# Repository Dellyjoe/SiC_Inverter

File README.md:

# SiC-Based Modular Inverter System

## Table of Contents
1. [Project Overview](#1-project-overview)  
2. [System Architecture](#2-system-architecture)  
   - [EMI Input Filter](#21-emi-input-filter)  
   - [Pre‑Charge & Inrush Limiting](#22-pre-charge--inrush-limiting)  
   - [DC‑Link Capacitor Network](#23-dc-link-capacitor-network)  
   - [Inverter Power Stage](#24-inverter-power-stage)  
   - [Output LCL Filter](#25-output-lcl-filter)  
3. [Electrical Specifications](#3-electrical-specifications)  
4. [Development Tools & Equipment](#4-development-tools--equipment)  
5. [Current Status](#5-current-status)  
6. [System Block Diagram](#6-system-block-diagram)

---

## 1. Project Overview

This project is a **modular, SiC‑based single‑phase inverter system** designed using professional engineering practices and a clean, hierarchical architecture. Each functional block is implemented as its own PCB, enabling:

- **Modularity** — swap, upgrade, or debug subsystems independently  
- **Scalability** — expand to higher power levels or new control architectures  
- **Serviceability** — isolate issues quickly during bring‑up  
- **Educational clarity** — each PCB teaches a specific power‑electronics concept  

Key design principles:

- **Hierarchical schematics** (KiCad 9)  
- **Modular PCBs** (EMI filter, pre‑charge, DC‑link, inverter legs, LCL filter, power supplies, controller)  
- **High‑performance SiC MOSFETs** for fast switching and low losses  
- **Low‑inductance DC‑link layout**  
- **Safe, lab‑friendly bring‑up** (initially 60 VDC)  

The long‑term goal is a **flexible, open inverter platform** suitable for experimentation, research, and future expansion.

---

## 2. System Architecture

The inverter is divided into well‑defined functional blocks.

### 2.1 EMI Input Filter
- Differential‑mode LC filter  
  - **L_DM:** `2300HT-470-H-RC`  
  - **C_IN:** `R71PI410050H6K`  
- Common‑mode choke: `7448258022`  
- Provides clean, low‑noise DC to downstream stages  
- **Outputs:** `BUS+_Filtered`, `BUS-_Filtered`

---

### 2.2 Pre‑Charge & Inrush Limiting
- Limits inrush current to **~5 A**  
- Uses an **80 Ω** pre‑charge resistor  
- MOSFET/relay bypass for full‑power operation  
- Interfaces between EMI filter and DC‑link  
- **Outputs:** `DC+`, `DC−`

---

### 2.3 DC‑Link Capacitor Network
- **Bulk Storage:** 220 µF electrolytic (10 × `ESH226M500AL4AA`)  
- **High‑Frequency Film:** 10 µF polypropylene (5 × `MKP1848C52050JK2`)  
- Provides:
  - Energy storage  
  - Low‑impedance switching current path  
  - Reduced ripple and overshoot  

---

### 2.4 Inverter Power Stage
- **Topology:** Full‑bridge using SiC MOSFET half‑bridge legs  
- **Switching Devices:** 4 × Wolfspeed `C3M0025065K`  
- **Gate Drivers:** 4 × TI `UCC21710QDWRQ1` isolated drivers  
- **Sensing:** Placeholders for output current and DC bus voltage (future work)  
- **Control:** PWM interface for microcontroller or DSP  

---

### 2.5 Output LCL Filter
- Shapes PWM into low‑distortion 60 Hz AC  
- Reduces switching ripple and protects the load  
- **Components:**
  - **Series Inductors:**  
    - `L1`: 470 µH (`Bourns 1140-471K-RC`)  
    - `L2`: 470 µH (`Bourns 1140-471K-RC`)  
  - **Shunt Capacitor:**  
    - `C_F`: 6.8 µF, 305 Vac MKP (`KEMET C4AF9BW4680T3FK`)  
  - **Damping Resistor:**  
    - `R_D`: ~10 Ω, ≥3 W (`TE 3-2176794-3`)  
- **Design Target:**  
  - Resonant frequency ≈ 2 kHz  
  - Damped to avoid resonance peaking  

---

## 3. Electrical Specifications

| Parameter | Value | Notes |
|----------|-------|-------|
| **Input Voltage Range** | 335–425 VDC | |
| **Nominal DC Bus Voltage** | 400 VDC | |
| **Output Voltage** | 120 Vrms | Single‑phase AC |
| **Output Frequency** | 60 Hz | |
| **Continuous Power** | 500 W | |
| **Peak Power** | 1 kW | |
| **Continuous Current (RMS)** | 4.1 Arms | Output |
| **Continuous Current (DC)** | 1.25 A | Input at nominal voltage |
| **Switching Frequency** | 40 kHz | Initial target |
| **Target Inrush Current** | < 5 A | Pre‑charge limited |
| **DC‑Link Capacitance** | 220 µF electrolytic + 10 µF film | |
| **Capacitor Voltage Rating** | >500 V | |
| **Output Filter Topology** | LCL | 470 µH – 6.8 µF – 470 µH |

---

## 4. Development Tools & Equipment
- **CAD:** KiCad 9 (hierarchical design)  
- **Version Control:** Git  
- **Documentation:** draw.io, Markdown  
- **Bench Tools:** Oscilloscope, isolated supplies, differential probes  
- *(More tools will be added as the project grows)*  

---

## 5. Current Status

- [x] EMI filter — **Complete**  
- [x] Pre‑charge topology — **Defined**  
- [x] DC‑link architecture — **Defined**  
- [x] KiCad hierarchy — **Modular & clean**  
- [x] Pre‑charge components added  
- [x] DC‑link capacitor bank added  
- [x] Inverter leg schematic started  
- [x] Output LCL filter populated with real parts  
- [x] Inverter + LCL interaction reviewed in simulation  
- [x] Power‑stage support rails (+15V ISO, +3V3 logic)  
- [x] Controller selected  
- [ ] Controller wiring  
- [ ] Layout of sub‑PCBs  
- [ ] System wiring and integration  

---

## 6. System Block Diagram

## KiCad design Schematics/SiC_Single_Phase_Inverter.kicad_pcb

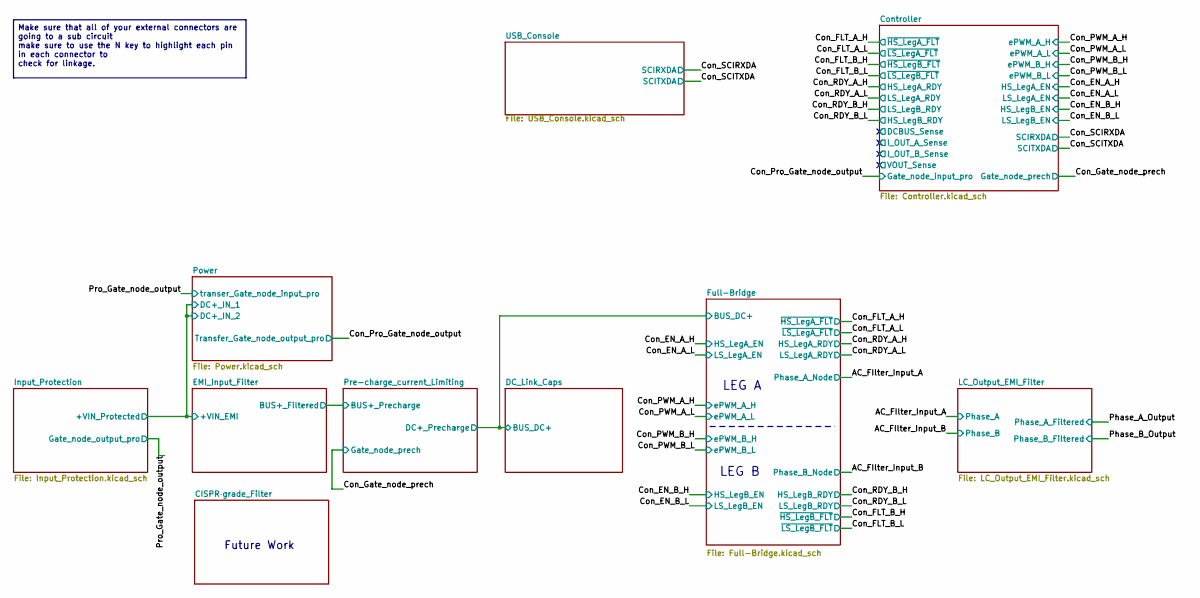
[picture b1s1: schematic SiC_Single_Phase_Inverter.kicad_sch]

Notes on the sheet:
LEG B
Future Work
LEG A
Make sure that all of your external connectors are going to a sub circuit make sure to use the N key to highlight each pin in each connector to check for linkage.

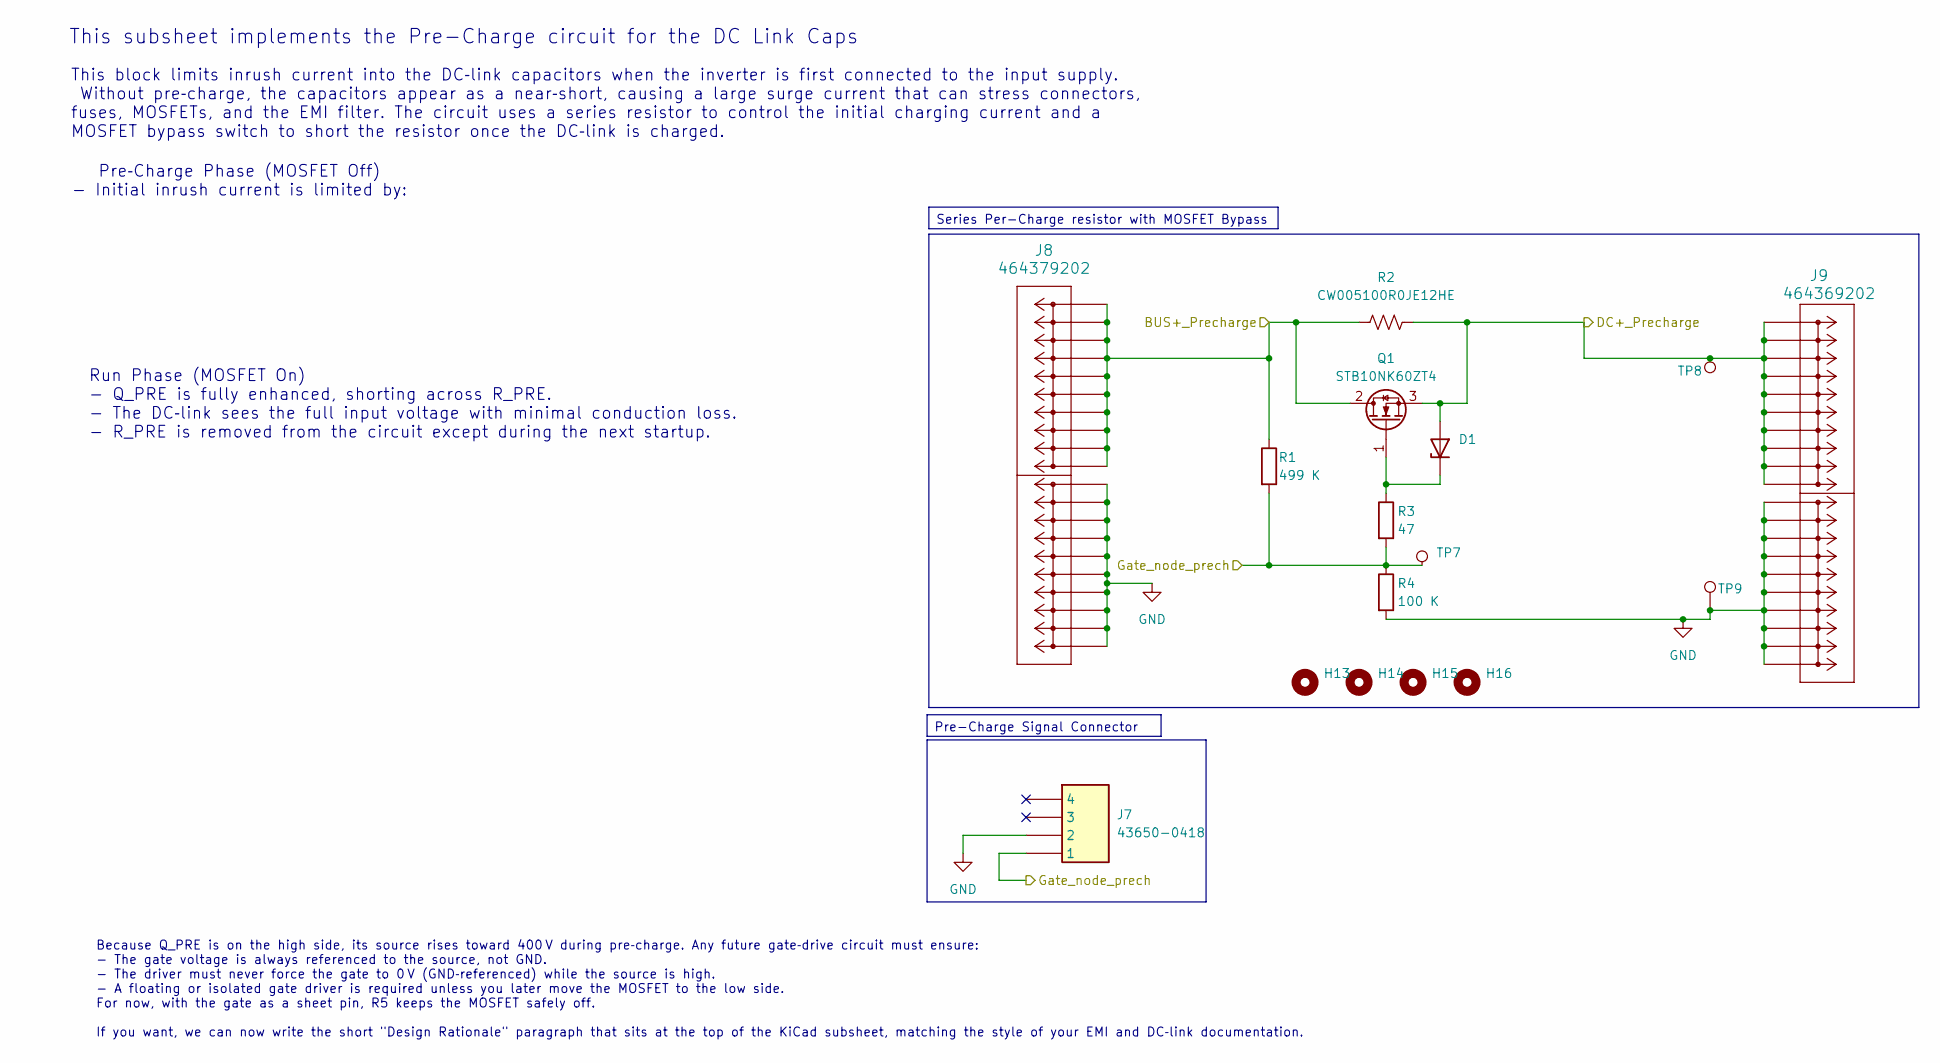
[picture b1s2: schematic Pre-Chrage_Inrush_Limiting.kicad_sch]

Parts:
D1: BZX84C15-7-F; SOT-23-3
H13, H14, H15, H16: MountingHole; MountingHole_2.2mm_M2
J7: 43650-0418; 436500418; Mouser Part Number 538-43650-0418
J8: 464379202; 46437-900_02
J9: 464369202; 46436-900_02
Q1: STB10NK60ZT4; TO-263-2
R1: 499 K; R_1206_3216Metric_Pad1.30x1.75mm_HandSolder
R2: CW005100R0JE12HE
R3: 47; R_1206_3216Metric_Pad1.30x1.75mm_HandSolder
R4: 100 K; R_1206_3216Metric_Pad1.30x1.75mm_HandSolder
TP7, TP8: 5277
TP9: 5281

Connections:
/Con_Gate_node_prech: J7.1, R1.2, R3.2, R4.1, TP7.1 (1_1); also elsewhere on the board
/DC_Link_Caps/BUS_DC+: D1.2 (A), J9.P1_1, J9.P1_2, J9.P1_3, J9.P1_4, J9.P1_5, J9.P1_6, J9.P1_7, J9.P1_8, J9.P1_9, J9.P1_10, Q1.3, R2.2, TP8.1 (1_1); also elsewhere on the board
/EMI_Input_Filter/BUS+_Filtered: J8.P2_1, J8.P2_2, J8.P2_3, J8.P2_4, J8.P2_5, J8.P2_6, J8.P2_7, J8.P2_8, J8.P2_9, J8.P2_10, Q1.2, R1.1, R2.1; also elsewhere on the board
GND: J7.2, J8.P1_1, J8.P1_2, J8.P1_3, J8.P1_4, J8.P1_5, J8.P1_6, J8.P1_7, J8.P1_8, J8.P1_9, J8.P1_10, J9.P2_1, J9.P2_2, J9.P2_3, J9.P2_4, J9.P2_5, J9.P2_6, J9.P2_7, J9.P2_8, J9.P2_9, J9.P2_10, R4.2, TP9.1 (1_1); also elsewhere on the board
unnamed: D1.1 (K), Q1.1 (G), R3.1

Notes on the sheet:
This block limits inrush current into the DC‑link capacitors when the inverter is first connected to the input supply. Without pre‑charge, the capacitors appear as a near‑short, causing a large surge current that can stress connectors, fuses, MOSFETs, and the EMI filter. The circuit uses a series r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
Pre‑Charge Phase (MOSFET Off) - Initial inrush current is limited by:
This subsheet implements the Pre-Charge circuit for the DC Link Caps
Run Phase (MOSFET On) - Q_PRE is fully enhanced, shorting across R_PRE. - The DC‑link sees the full input voltage with minimal conduction loss. - R_PRE is removed from the circuit except during the next startup.
Because Q_PRE is on the high side, its source rises toward 400 V during pre‑charge. Any future gate‑drive circuit must ensure: - The gate voltage is always referenced to the source, not GND. - The driver must never force the gate to 0 V (GND‑referenced) while the source is high. - A floating or iso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
Series Per-Charge resistor with MOSFET Bypass
Pre-Charge Signal Connector

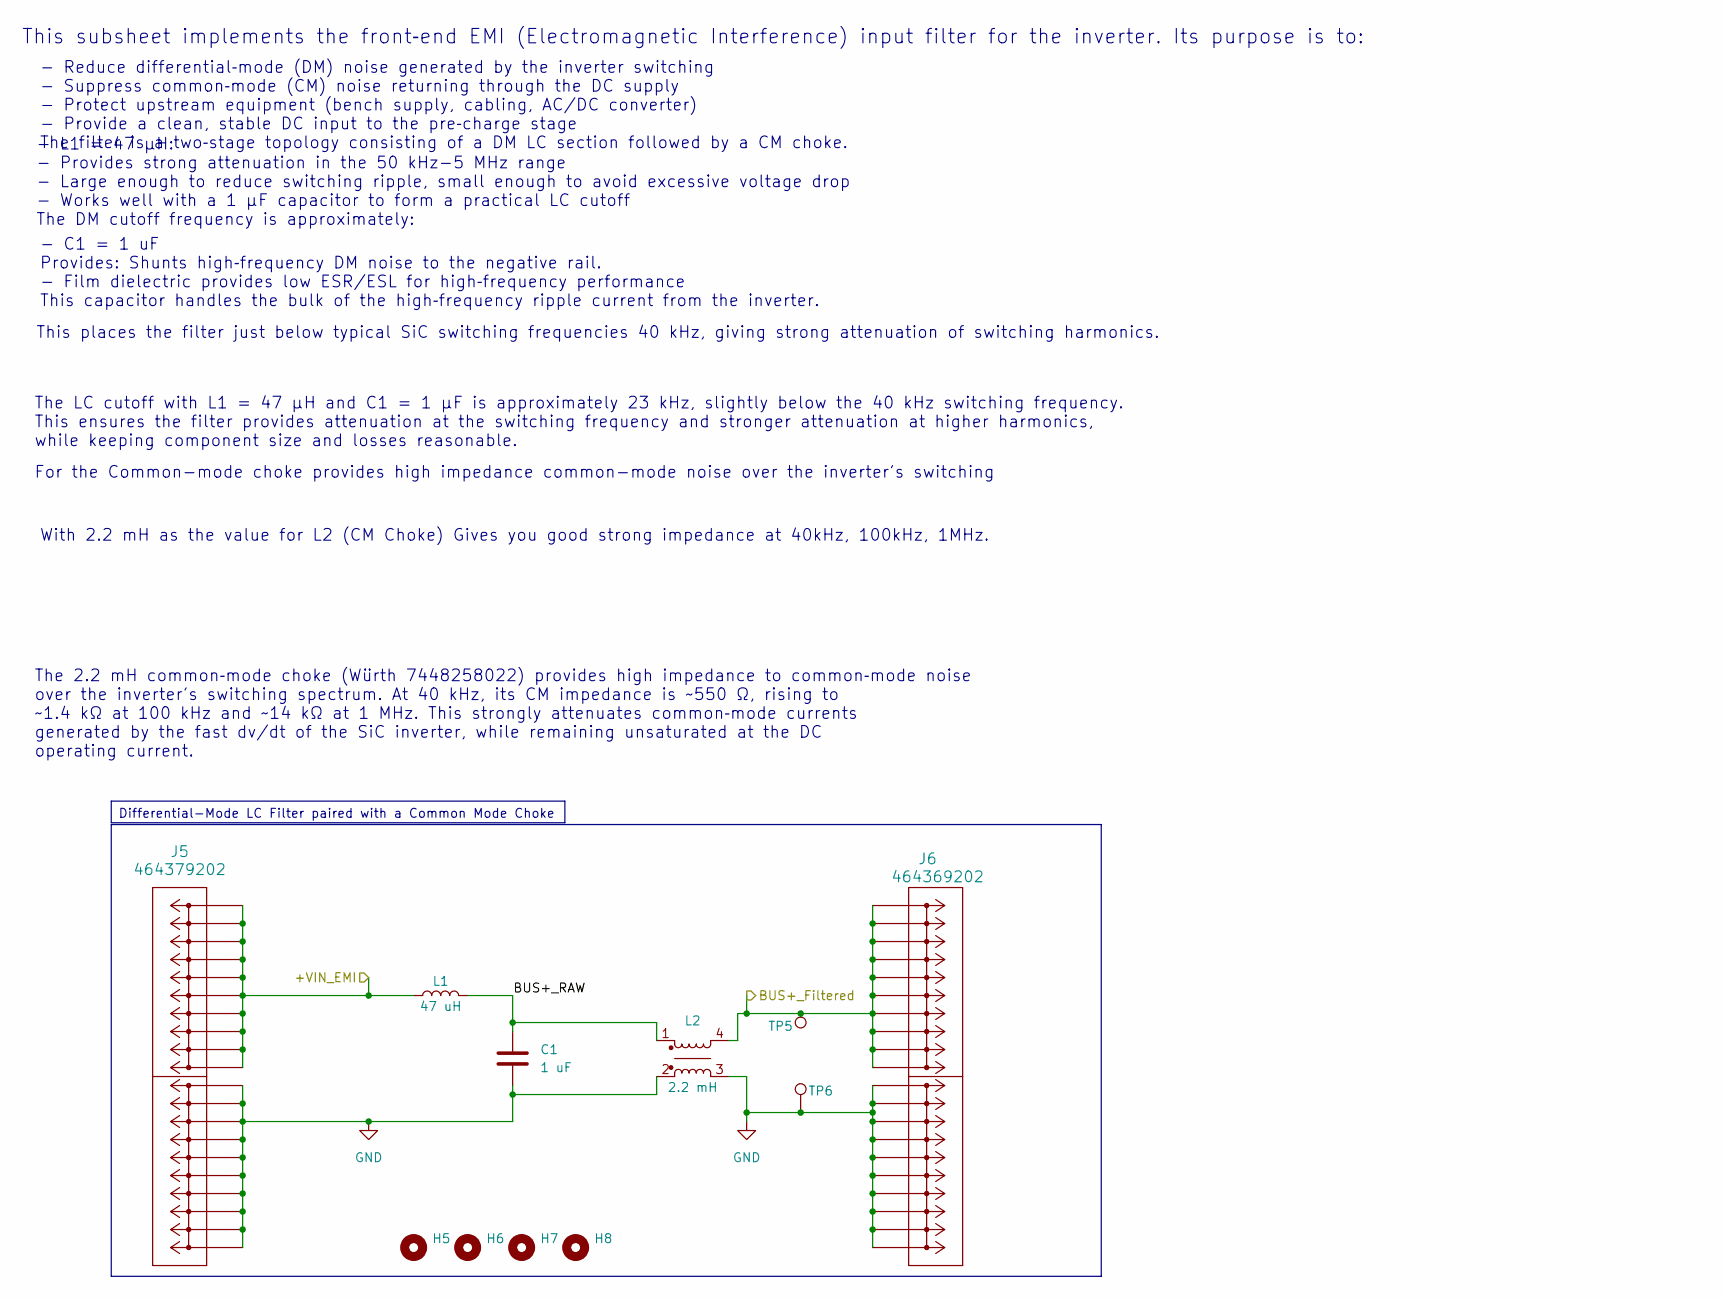
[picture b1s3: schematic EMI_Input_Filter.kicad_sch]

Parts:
C1: 1 uF; R71PI410050H6K
H5, H6, H7, H8: MountingHole; MountingHole_2.2mm_M2
J5: 464379202; 46437-900_02
J6: 464369202; 46436-900_02
L1: 47 uH; 2300HT_470
L2: 2.2 mH; 7448258022
TP5: 5277
TP6: 5281

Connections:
/EMI_Input_Filter/+VIN_EMI: J5.P2_1, J5.P2_2, J5.P2_3, J5.P2_4, J5.P2_5, J5.P2_6, J5.P2_7, J5.P2_8, J5.P2_9, J5.P2_10, L1.1; also elsewhere on the board
/EMI_Input_Filter/BUS+_Filtered: J6.P1_1, J6.P1_2, J6.P1_3, J6.P1_4, J6.P1_5, J6.P1_6, J6.P1_7, J6.P1_8, J6.P1_9, J6.P1_10, L2.4, TP5.1 (1_1); also elsewhere on the board
/EMI_Input_Filter/BUS+_RAW: C1.1, L1.2, L2.1
GND: C1.2, J5.P1_1, J5.P1_2, J5.P1_3, J5.P1_4, J5.P1_5, J5.P1_6, J5.P1_7, J5.P1_8, J5.P1_9, J5.P1_10, J6.P2_1, J6.P2_2, J6.P2_3, J6.P2_4, J6.P2_5, J6.P2_6, J6.P2_7, J6.P2_8, J6.P2_9, J6.P2_10, L2.2, L2.3, TP6.1 (1_1); also elsewhere on the board

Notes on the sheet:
This subsheet implements the front‑end EMI (Electromagnetic Interference) input filter for the inverter. Its purpose is to:
- L1 = 47 µH: - Provides strong attenuation in the 50 kHz-5 MHz range - Large enough to reduce switching ripple, small enough to avoid excessive voltage drop - Works well with a 1 µF capacitor to form a practical LC cutoff The DM cutoff frequency is approximately: This places the filter just below 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
- Reduce differential‑mode (DM) noise generated by the inverter switching - Suppress common‑mode (CM) noise returning through the DC supply - Protect upstream equipment (bench supply, cabling, AC/DC converter) - Provide a clean, stable DC input to the pre‑charge stage The filter is a two‑stage topo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
The 2.2 mH common‑mode choke (Würth 7448258022) provides high impedance to common‑mode noise over the inverter's switching spectrum. At 40 kHz, its CM impedance is ~550 Ω, rising to ~1.4 kΩ at 100 kHz and ~14 kΩ at 1 MHz. This strongly attenuates common‑mode currents generated by the fast dv/dt of 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
The LC cutoff with L1 = 47 µH and C1 = 1 µF is approximately 23 kHz, slightly below the 40 kHz switching frequency. This ensures the filter provides attenuation at the switching frequency and stronger attenuation at higher harmonics, while keeping component size and losses reasonable.
For the Common-mode choke provides high impedance common-mode noise over the inverter's switching
With 2.2 mH as the value for L2 (CM Choke) Gives you good strong impedance at 40kHz, 100kHz, 1MHz.
- C1 = 1 uF Provides: Shunts high‑frequency DM noise to the negative rail. - Film dielectric provides low ESR/ESL for high‑frequency performance This capacitor handles the bulk of the high‑frequency ripple current from the inverter.
Differential-Mode LC Filter paired with a Common Mode Choke

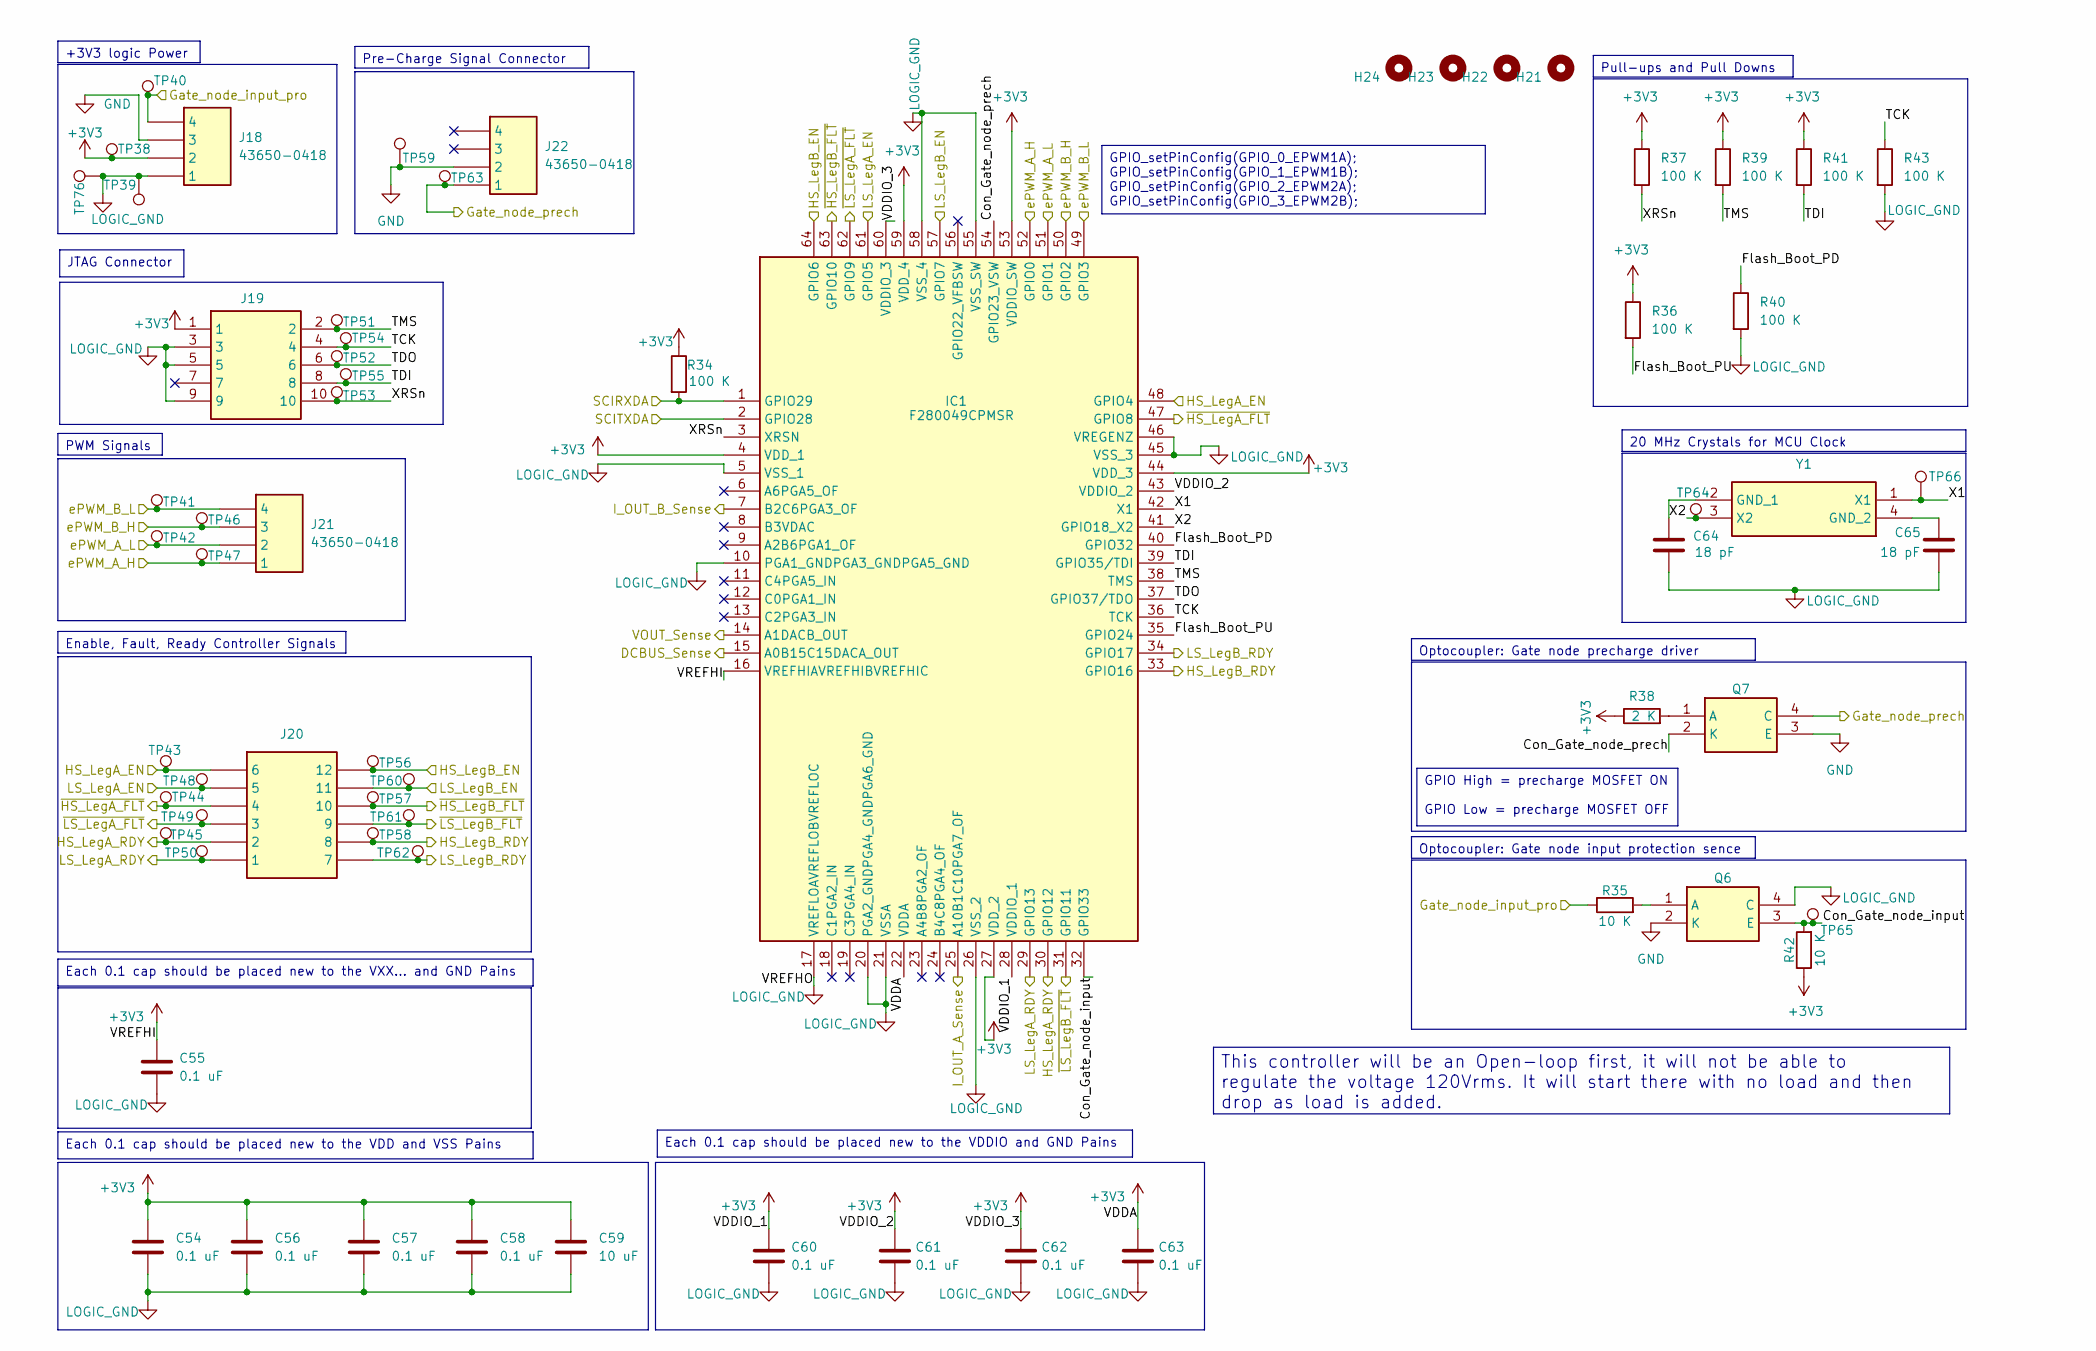
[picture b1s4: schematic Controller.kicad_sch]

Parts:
C54, C55, C56, C57, C58, C60, C61, C62, C63: 0.1 uF; C_0805_2012Metric_Pad1.18x1.45mm_HandSolder
C59: 10 uF; C_0805_2012Metric_Pad1.18x1.45mm_HandSolder
C64, C65: 18 pF; C_0402_1005Metric_Pad0.74x0.62mm_HandSolder
H21, H22, H23, H24: MountingHole; MountingHole_2.2mm_M2
IC1: F280049CPMSR; Mouser Part Number 595-F280049CPMSR
J18, J21, J22: 43650-0418; 436500418; Mouser Part Number 538-43650-0418
J19: FTSH-105-01-LM-D-K; Manufacturer_Part_Number FTSH-105-01-LM-D-K
J20: 43045-1212; Mouser Part Number 538-43045-1212
Q6, Q7: PC817X1CSP9F; Mouser Part Number 852-PC817X1CSP9F
R34, R36, R37, R39, R40, R41, R43: 100 K; R_1206_3216Metric_Pad1.30x1.75mm_HandSolder
R35, R42: 10 K; R_1206_3216Metric_Pad1.30x1.75mm_HandSolder
R38: 2 K; R_1206_3216Metric_Pad1.30x1.75mm_HandSolder
TP38, TP40, TP41, TP42, TP43, TP44, TP45, TP46, TP47, TP48, TP49, TP50, TP51, TP52, TP53, TP54, TP55, TP56, TP57, TP58, TP60, TP61, TP62, TP63, TP64, TP65: 5277
TP39, TP59, TP66, TP76: 5281
Y1: ABM8-20.000MHZ-B2-T; Mouser Part Number 815-ABM8-20-B2-T

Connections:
+3V3: C54.1, C55.1, C56.1, C57.1, C58.1, C59.1, C60.1, C61.1, C62.1, C63.1, IC1.4 (VDD_1), IC1.16 (VREFHIAVREFHIBVREFHIC), IC1.22 (VDDA), IC1.27 (VDD_2), IC1.28 (VDDIO_1), IC1.43 (VDDIO_2), IC1.44 (VDD_3), IC1.53 (VDDIO_SW), IC1.59 (VDD_4), IC1.60 (VDDIO_3), J18.2, J19.1, R34.1, R36.1, R37.1, R38.1, R39.1, R41.1, R42.1, TP38.1 (1_1); also elsewhere on the board
/Con_EN_A_H: IC1.48 (GPIO4), J20.6, TP43.1 (1_1); also elsewhere on the board
/Con_EN_A_L: IC1.61 (GPIO5), J20.5, TP48.1 (1_1); also elsewhere on the board
/Con_EN_B_H: IC1.64 (GPIO6), J20.12, TP56.1 (1_1); also elsewhere on the board
/Con_EN_B_L: IC1.57 (GPIO7), J20.11, TP60.1 (1_1); also elsewhere on the board
/Con_FLT_A_H: IC1.47 (GPIO8), J20.4, TP44.1 (1_1); also elsewhere on the board
/Con_FLT_A_L: IC1.62 (GPIO9), J20.3, TP49.1 (1_1); also elsewhere on the board
/Con_FLT_B_H: IC1.63 (GPIO10), J20.10, TP57.1 (1_1); also elsewhere on the board
/Con_FLT_B_L: IC1.31 (GPIO11), J20.9, TP61.1 (1_1); also elsewhere on the board
/Con_Gate_node_prech: J22.1, Q7.4 (C), TP63.1 (1_1); also elsewhere on the board
/Con_PWM_A_H: IC1.52 (GPIO0), J21.1, TP47.1 (1_1); also elsewhere on the board
/Con_PWM_A_L: IC1.51 (GPIO1), J21.2, TP42.1 (1_1); also elsewhere on the board
/Con_PWM_B_H: IC1.50 (GPIO2), J21.3, TP46.1 (1_1); also elsewhere on the board
/Con_PWM_B_L: IC1.49 (GPIO3), J21.4, TP41.1 (1_1); also elsewhere on the board
/Con_Pro_Gate_node_output: J18.4, R35.1, TP40.1 (1_1); also elsewhere on the board
/Con_RDY_A_H: IC1.30 (GPIO12), J20.2, TP45.1 (1_1); also elsewhere on the board
/Con_RDY_A_L: IC1.29 (GPIO13), J20.1, TP50.1 (1_1); also elsewhere on the board
/Con_RDY_B_H: IC1.34 (GPIO17), J20.7, TP62.1 (1_1); also elsewhere on the board
/Con_RDY_B_L: IC1.33 (GPIO16), J20.8, TP58.1 (1_1); also elsewhere on the board
/Con_SCIRXDA: IC1.1 (GPIO29), R34.2; also elsewhere on the board
/Con_SCITXDA: IC1.2 (GPIO28); also elsewhere on the board
/Controller/Con_Gate_node_input: IC1.32 (GPIO33), Q6.3 (E), R42.2, TP65.1 (1_1)
/Controller/Con_Gate_node_prech: IC1.54 (GPIO23_VSW), Q7.2 (K)
/Controller/DCBUS_Sense: IC1.15 (A0B15C15DACA_OUT)
/Controller/Flash_Boot_PD: IC1.40 (GPIO32), R40.1
/Controller/Flash_Boot_PU: IC1.35 (GPIO24), R36.2
/Controller/I_OUT_A_Sense: IC1.25 (A10B1C10PGA7_OF)
/Controller/I_OUT_B_Sense: IC1.7 (B2C6PGA3_OF)
/Controller/TCK: IC1.36 (TCK), J19.4, R43.1, TP54.1 (1_1)
/Controller/TDI: IC1.39 (GPIO35/TDI), J19.8, R41.2, TP55.1 (1_1)
/Controller/TDO: IC1.37 (GPIO37/TDO), J19.6, TP52.1 (1_1)
/Controller/TMS: IC1.38 (TMS), J19.2, R39.2, TP51.1 (1_1)
/Controller/VOUT_Sense: IC1.14 (A1DACB_OUT)
/Controller/X1: IC1.42 (X1), TP66.1 (1_1), Y1.1 (X1)
/Controller/X2: IC1.41 (GPIO18_X2), TP64.1 (1_1), Y1.3 (X2)
/Controller/XRSn: IC1.3 (XRSN), J19.10, R37.2, TP53.1 (1_1)
GND: J18.3, J22.2, Q6.2 (K), Q7.3 (E), TP59.1 (1_1); also elsewhere on the board
LOGIC_GND: C54.2, C55.2, C56.2, C57.2, C58.2, C59.2, C60.2, C61.2, C62.2, C63.2, C64.2, C65.2, IC1.5 (VSS_1), IC1.10 (PGA1_GNDPGA3_GNDPGA5_GND), IC1.17 (VREFLOAVREFLOBVREFLOC), IC1.20 (PGA2_GNDPGA4_GNDPGA6_GND), IC1.21 (VSSA), IC1.26 (VSS_2), IC1.45 (VSS_3), IC1.46 (VREGENZ), IC1.55 (VSS_SW), IC1.58 (VSS_4), J18.1, J19.3, J19.5, J19.9, Q6.4 (C), R40.2, R43.2, TP39.1 (1_1), TP76.1 (1_1); also elsewhere on the board
unnamed: Q6.1 (A), R35.2
unnamed: Q7.1 (A), R38.2
unnamed: C64.1, Y1.2 (GND_1)
unnamed: C65.1, Y1.4 (GND_2)

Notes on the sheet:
Pull-ups and Pull Downs
GPIO_setPinConfig(GPIO_0_EPWM1A); GPIO_setPinConfig(GPIO_1_EPWM1B); GPIO_setPinConfig(GPIO_2_EPWM2A); GPIO_setPinConfig(GPIO_3_EPWM2B);
Pre-Charge Signal Connector
Each 0.1 cap should be placed new to the VDDIO and GND Pains
Enable, Fault, Ready Controller Signals
Each 0.1 cap should be placed new to the VXX... and GND Pains
20 MHz Crystals for MCU Clock
PWM Signals
This controller will be an Open-loop first, it will not be able to regulate the voltage 120Vrms. It will start there with no load and then drop as load is added.
JTAG Connector
Optocoupler: Gate node precharge driver
Optocoupler: Gate node input protection sence
Each 0.1 cap should be placed new to the VDD and VSS Pains
GPIO High = precharge MOSFET ON GPIO Low = precharge MOSFET OFF
+3V3 logic Power

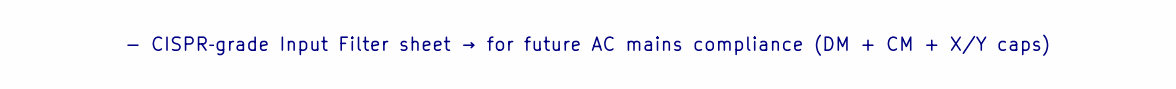
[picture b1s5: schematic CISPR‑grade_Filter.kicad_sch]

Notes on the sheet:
- CISPR‑grade Input Filter sheet → for future AC mains compliance (DM + CM + X/Y caps)

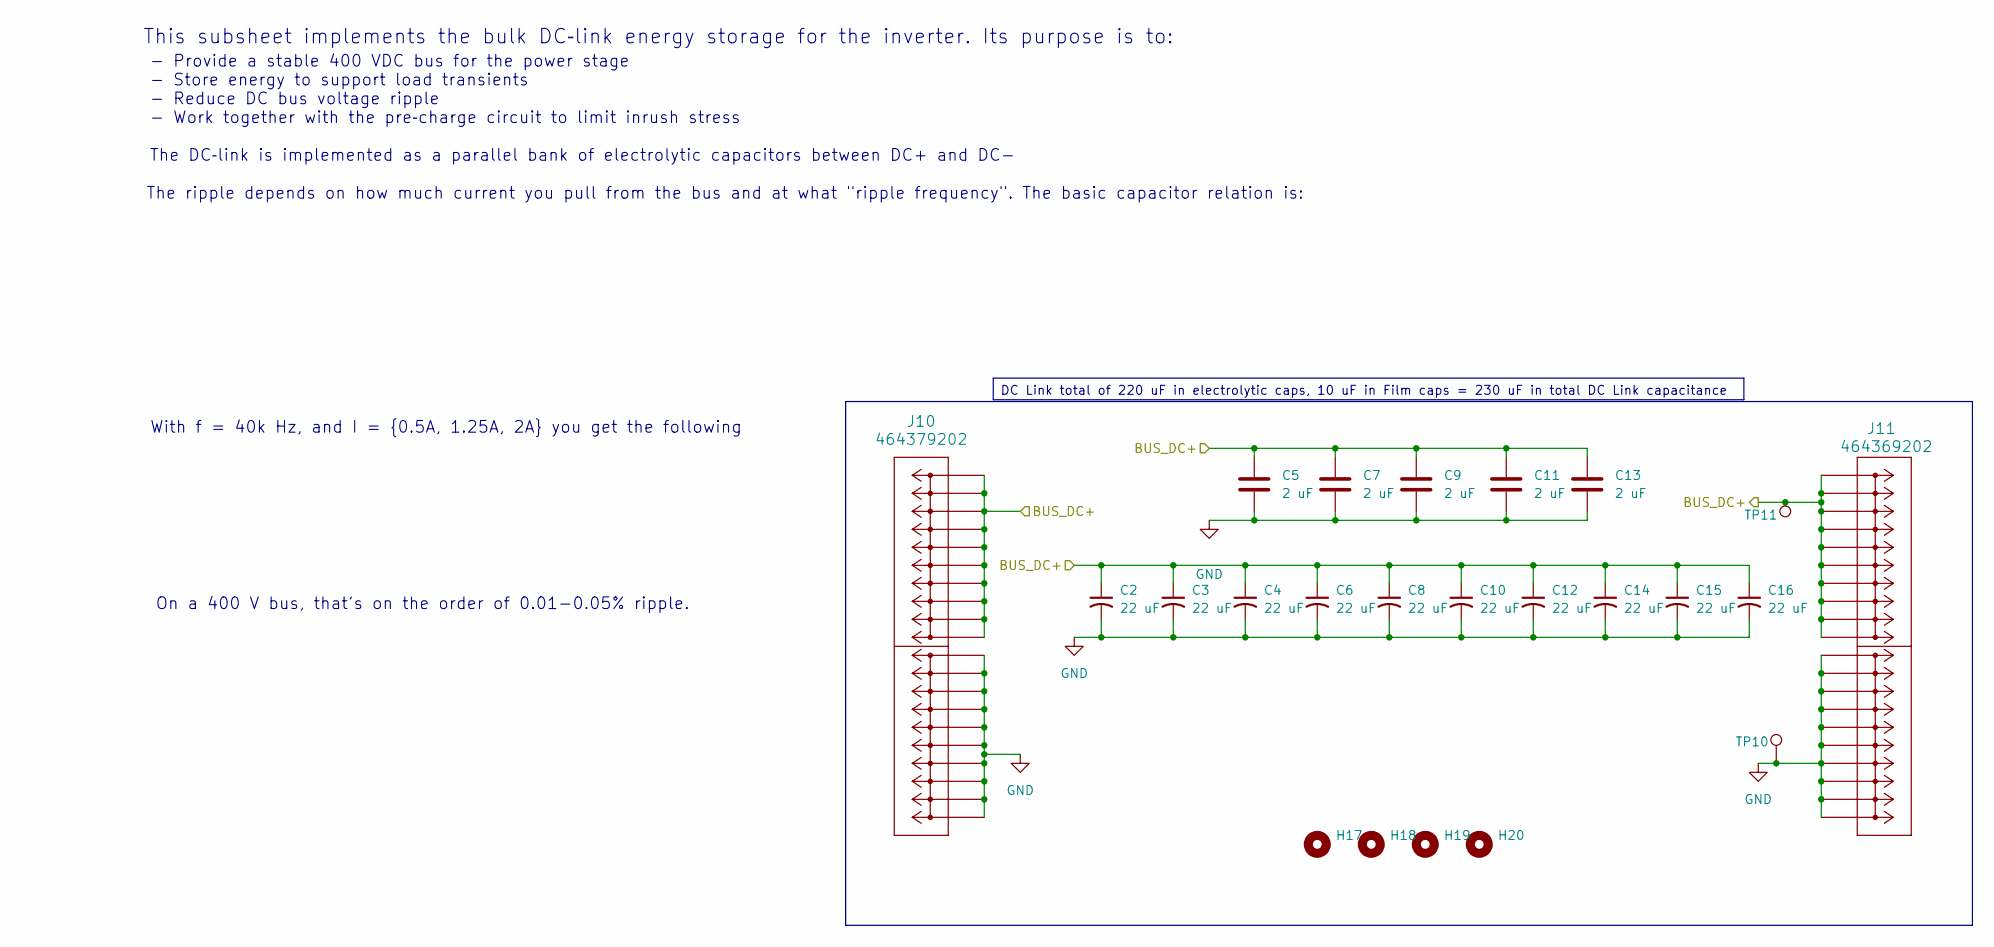
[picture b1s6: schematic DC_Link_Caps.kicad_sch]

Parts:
C2, C3, C4, C6, C8, C10, C12, C14, C15, C16: 22 uF; ESH226M500AL4AA
C5, C7, C9, C11, C13: 2 uF; MKP1848C52050JK2
H17, H18, H19, H20: MountingHole; MountingHole_2.2mm_M2
J10: 464379202; 46437-900_02
J11: 464369202; 46436-900_02
TP10: 5281
TP11: 5277

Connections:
/DC_Link_Caps/BUS_DC+: C2.1, C3.1, C4.1, C5.1, C6.1, C7.1, C8.1, C9.1, C10.1, C11.1, C12.1, C13.1, C14.1, C15.1, C16.1, J10.P2_1, J10.P2_2, J10.P2_3, J10.P2_4, J10.P2_5, J10.P2_6, J10.P2_7, J10.P2_8, J10.P2_9, J10.P2_10, J11.P1_1, J11.P1_2, J11.P1_3, J11.P1_4, J11.P1_5, J11.P1_6, J11.P1_7, J11.P1_8, J11.P1_9, J11.P1_10, TP11.1 (1_1); also elsewhere on the board
GND: C2.2, C3.2, C4.2, C5.2, C6.2, C7.2, C8.2, C9.2, C10.2, C11.2, C12.2, C13.2, C14.2, C15.2, C16.2, J10.P1_1, J10.P1_2, J10.P1_3, J10.P1_4, J10.P1_5, J10.P1_6, J10.P1_7, J10.P1_8, J10.P1_9, J10.P1_10, J11.P2_1, J11.P2_2, J11.P2_3, J11.P2_4, J11.P2_5, J11.P2_6, J11.P2_7, J11.P2_8, J11.P2_9, J11.P2_10, TP10.1 (1_1); also elsewhere on the board

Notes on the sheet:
- Provide a stable 400 VDC bus for the power stage - Store energy to support load transients - Reduce DC bus voltage ripple - Work together with the pre‑charge circuit to limit inrush stress The DC‑link is implemented as a parallel bank of electrolytic capacitors between DC+ and DC−
With f = 40k Hz, and I = {0.5A, 1.25A, 2A} you get the following
This subsheet implements the bulk DC‑link energy storage for the inverter. Its purpose is to:
On a 400 V bus, that's on the order of 0.01-0.05% ripple.
The ripple depends on how much current you pull from the bus and at what "ripple frequency". The basic capacitor relation is:
DC Link total of 220 uF in electrolytic caps, 10 uF in Film caps = 230 uF in total DC Link capacitance

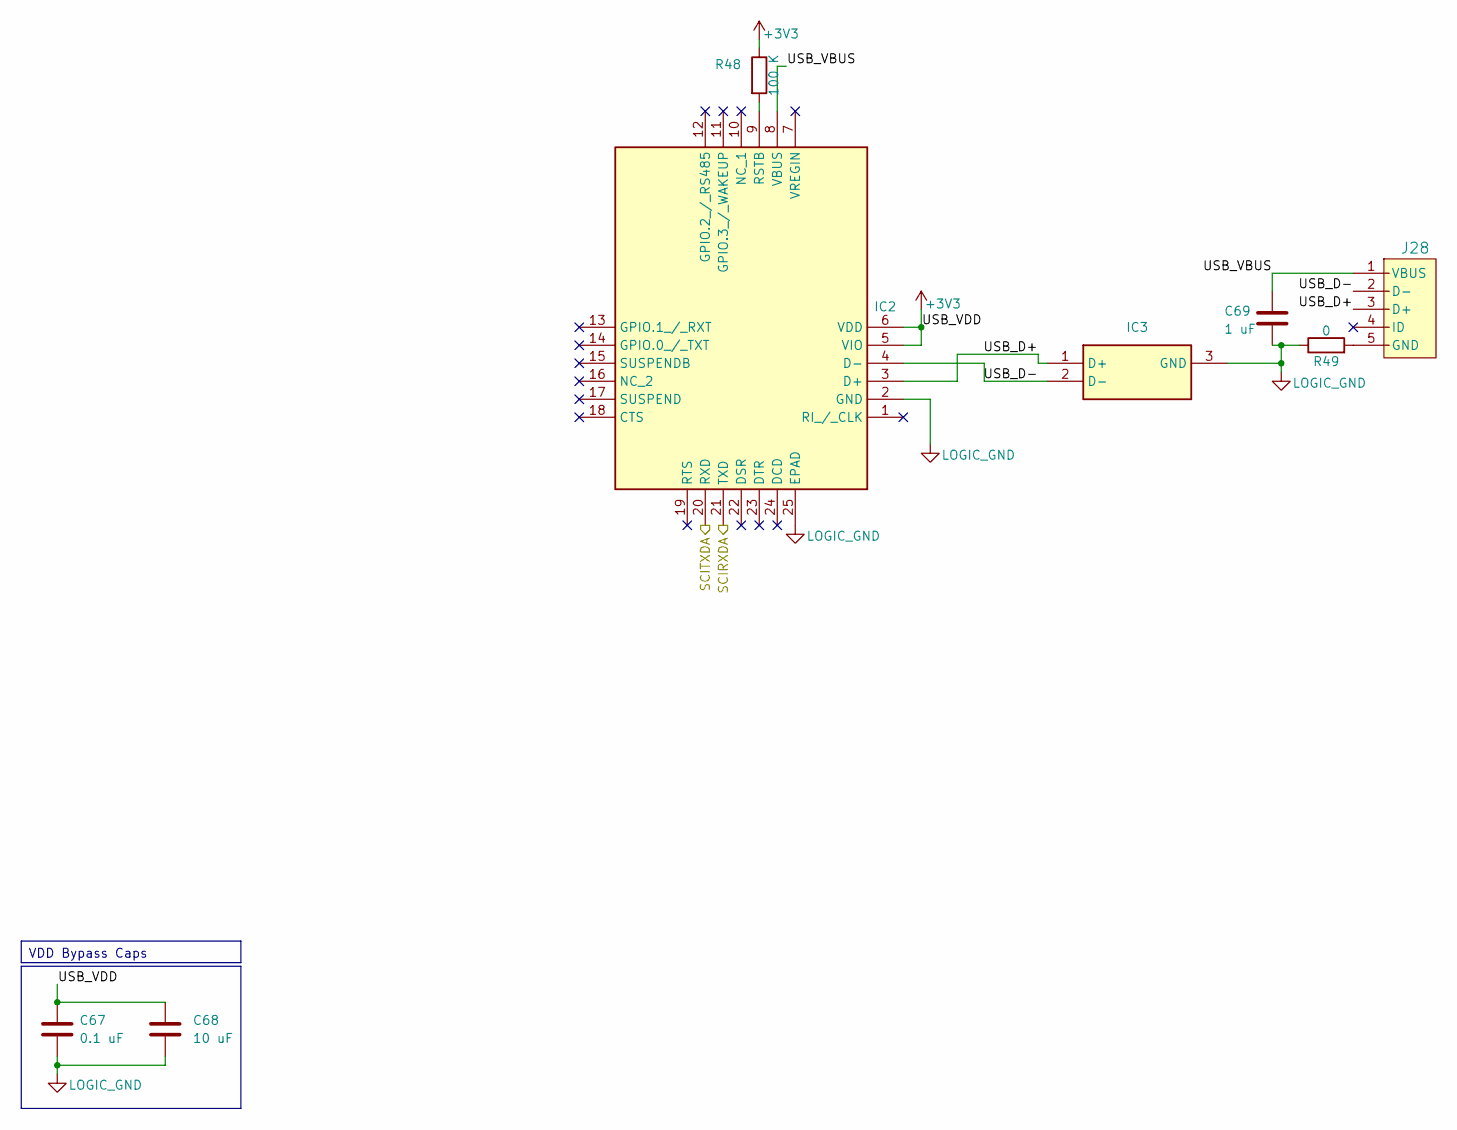
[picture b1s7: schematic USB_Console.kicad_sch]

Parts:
C67: 0.1 uF; C_0805_2012Metric_Pad1.18x1.45mm_HandSolder
C68: 10 uF; C_0805_2012Metric_Pad1.18x1.45mm_HandSolder
C69: 1 uF; C_1206_3216Metric_Pad1.33x1.80mm_HandSolder
IC2: CP2102N-A02-GQFN24R; Mouser Part Number 634-CP2102NA02QFN24R
IC3: TPD2EUSB30ADRTR; Mouser Part Number 595-TPD2EUSB30ADRTR
J28: 1051330011; 105133-0011
R48: 100 K; R_1206_3216Metric_Pad1.30x1.75mm_HandSolder
R49: 0; R_1206_3216Metric_Pad1.30x1.75mm_HandSolder

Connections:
+3V3: C67.1, C68.1, IC2.5 (VIO), IC2.6 (VDD), R48.1; also elsewhere on the board
/Con_SCIRXDA: IC2.21 (TXD); also elsewhere on the board
/Con_SCITXDA: IC2.20 (RXD); also elsewhere on the board
/USB_Console/USB_D+: IC2.3 (D+), IC3.1 (D+), J28.3 (D+)
/USB_Console/USB_D-: IC2.4 (D-), IC3.2 (D-), J28.2 (D-)
/USB_Console/USB_VBUS: C69.1, IC2.8 (VBUS), J28.1 (VBUS)
LOGIC_GND: C67.2, C68.2, C69.2, IC2.2 (GND), IC2.25 (EPAD), IC3.3 (GND), R49.1; also elsewhere on the board
unnamed: IC2.9 (RSTB), R48.2
unnamed: J28.5 (GND), R49.2

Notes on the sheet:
VDD Bypass Caps
